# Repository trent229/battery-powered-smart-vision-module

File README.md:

# Battery-Powered Smart Vision Module

## Overview

The Battery-Powered Smart Vision Module is a compact embedded vision system built around the Seeed Studio XIAO ESP32S3 Sense. The project demonstrates battery-powered embedded design, Wi-Fi camera streaming, and low-power operation for robotics and remote monitoring applications.

This project serves as the foundation for the Sure Sight Security platform while demonstrating embedded systems engineering principles including power management, schematic design, firmware development, and hardware integration.

---

## Project Objectives

- Design a battery-powered embedded vision module.
- Stream live video over Wi-Fi.
- Operate from a rechargeable LiPo battery.
- Develop custom hardware for production.
- Demonstrate professional embedded engineering documentation.

---

## Course Outcomes

This project demonstrates:

- Embedded microcontroller selection
- Battery-powered embedded design
- Camera integration
- Vision sensing
- Schematic development
- PCB development
- Embedded firmware
- Professional engineering documentation

---

## Hardware

- Seeed Studio XIAO ESP32S3 Sense
- OV2640 Camera
- 3.7V LiPo Battery
- USB-C Charging
- Wi-Fi Connectivity

---

## Software

- Arduino IDE
- ESP32 Arduino Framework
- Git
- GitHub
- Visual Studio Code

---

## Repository Structure

```
docs/
firmware/
hardware/
media/
website/
```

---

## Current Status

🟢 Repository Created

🟢 Initial Folder Structure Complete

🟡 Hardware Design In Progress

⚪ PCB Design

⚪ Firmware Development

⚪ Testing

⚪ Final Documentation

---

## Future Improvements

- Battery Monitoring
- Motion Detection
- Custom PCB
- Improved Camera Module
- Power Optimization
- Weather Resistant Enclosure

---

## License

MIT License

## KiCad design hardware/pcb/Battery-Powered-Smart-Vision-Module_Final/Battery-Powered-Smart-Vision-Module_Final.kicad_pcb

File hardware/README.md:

# Battery-Powered Smart Vision Module

## Hardware

- XIAO ESP32S3 Sense
- LiPo Battery
- USB-C Charging

## Features

- Battery powered
- Wi-Fi camera
- Motion detection

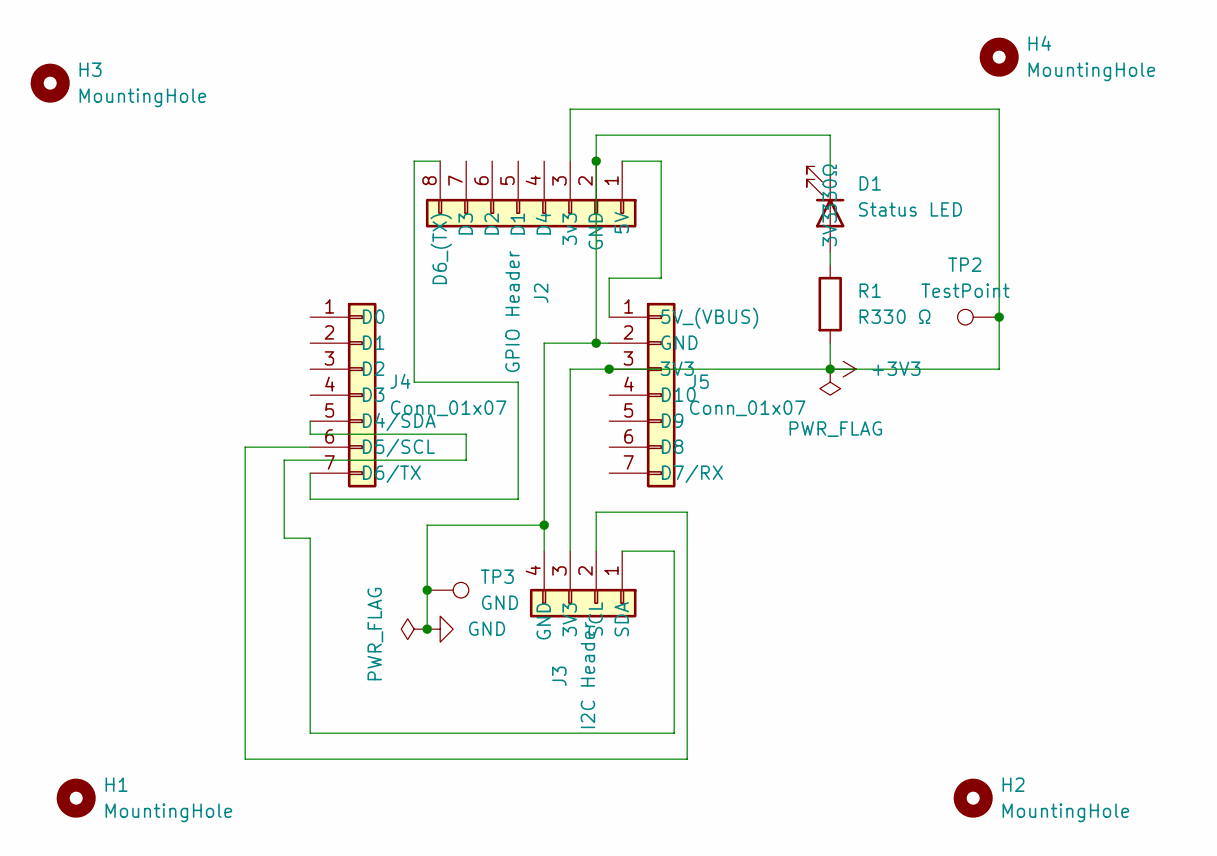
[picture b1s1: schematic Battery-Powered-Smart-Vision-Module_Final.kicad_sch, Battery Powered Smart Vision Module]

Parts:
D1: Status LED; LED_D5.0mm
H1, H2, H3, H4: MountingHole; MountingHole_3.2mm_M3
J2: GPIO Header; PinHeader_1x08_P2.54mm_Vertical
J3: I2C Header; PinHeader_1x04_P2.54mm_Vertical
J4, J5: Conn_01x07; PinHeader_1x07_P2.54mm_Vertical
R1: R330 Ω; R_Axial_DIN0207_L6.3mm_D2.5mm_P7.62mm_Horizontal
TP2: TestPoint; TestPoint_Loop_D3.80mm_Drill2.8mm
TP3: GND; TestPoint_Loop_D3.80mm_Drill2.8mm

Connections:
+3V3: J2.3 (3v3), J3.3 (3V3), J5.3 (3V3), R1.2, TP2.1 (1_1)
GND: D1.1 (3V3), J2.2 (GND), J3.4 (GND), J5.2 (GND), TP3.1 (1_1)
unnamed: D1.2 (330Ω), R1.1
unnamed: J2.1 (5V), J5.1 (5V_(VBUS))
unnamed: J2.8 (D6_(TX)), J4.7 (D6/TX)
unnamed: J3.2 (SCL), J4.6 (D5/SCL)
unnamed: J3.1 (SDA), J4.5 (D4/SDA)

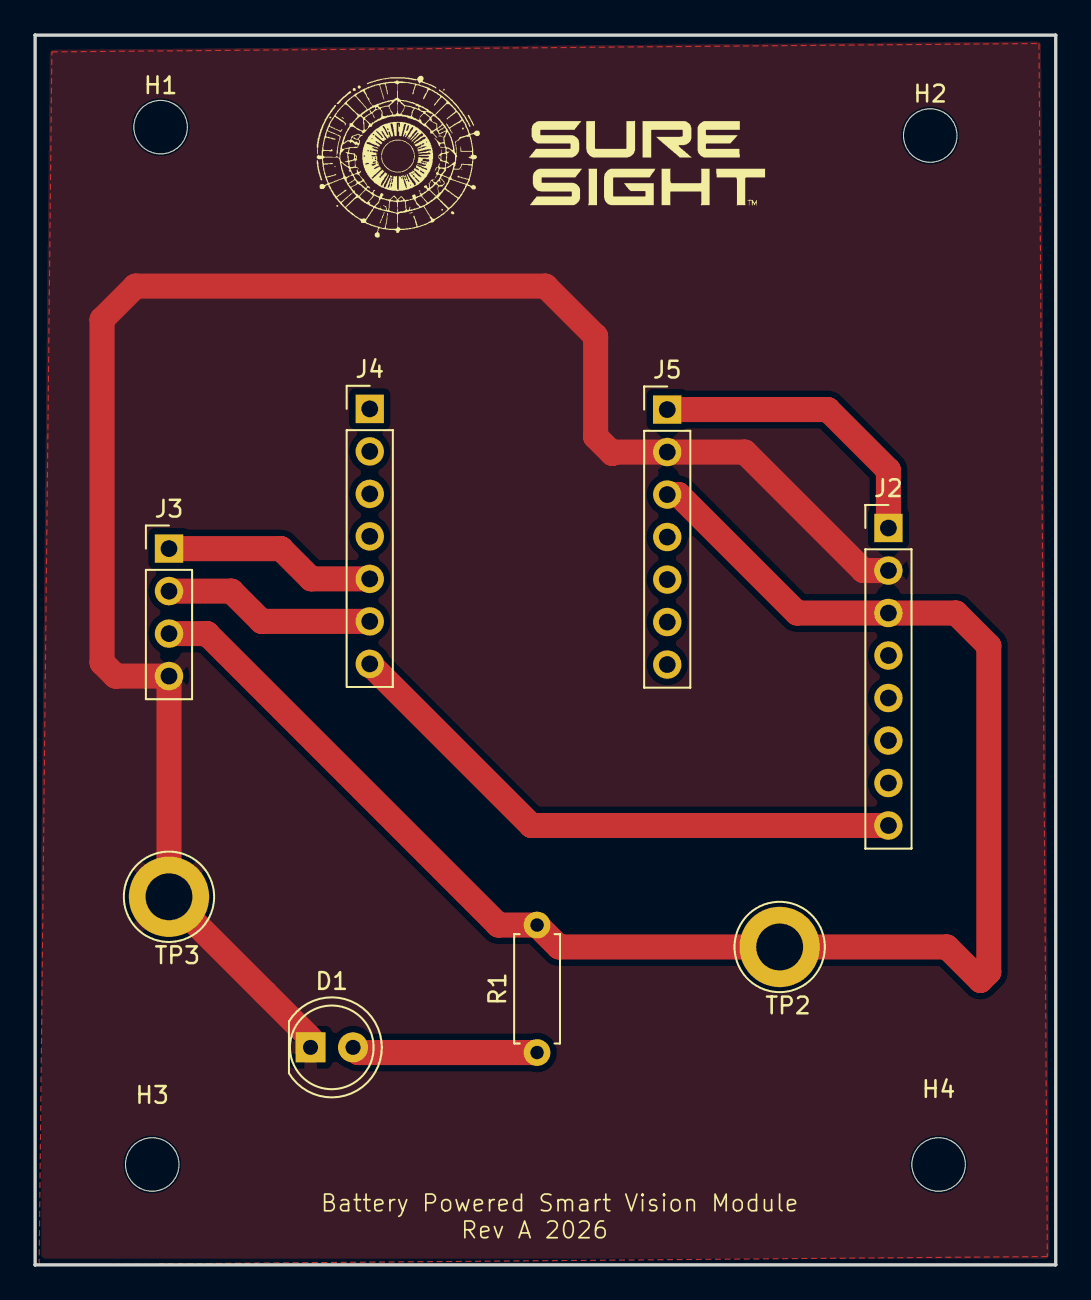
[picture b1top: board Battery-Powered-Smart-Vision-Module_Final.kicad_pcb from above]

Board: 2 copper layers, 61.0 x 73.5 mm, 12 parts (0 on the bottom side), 7 nets.

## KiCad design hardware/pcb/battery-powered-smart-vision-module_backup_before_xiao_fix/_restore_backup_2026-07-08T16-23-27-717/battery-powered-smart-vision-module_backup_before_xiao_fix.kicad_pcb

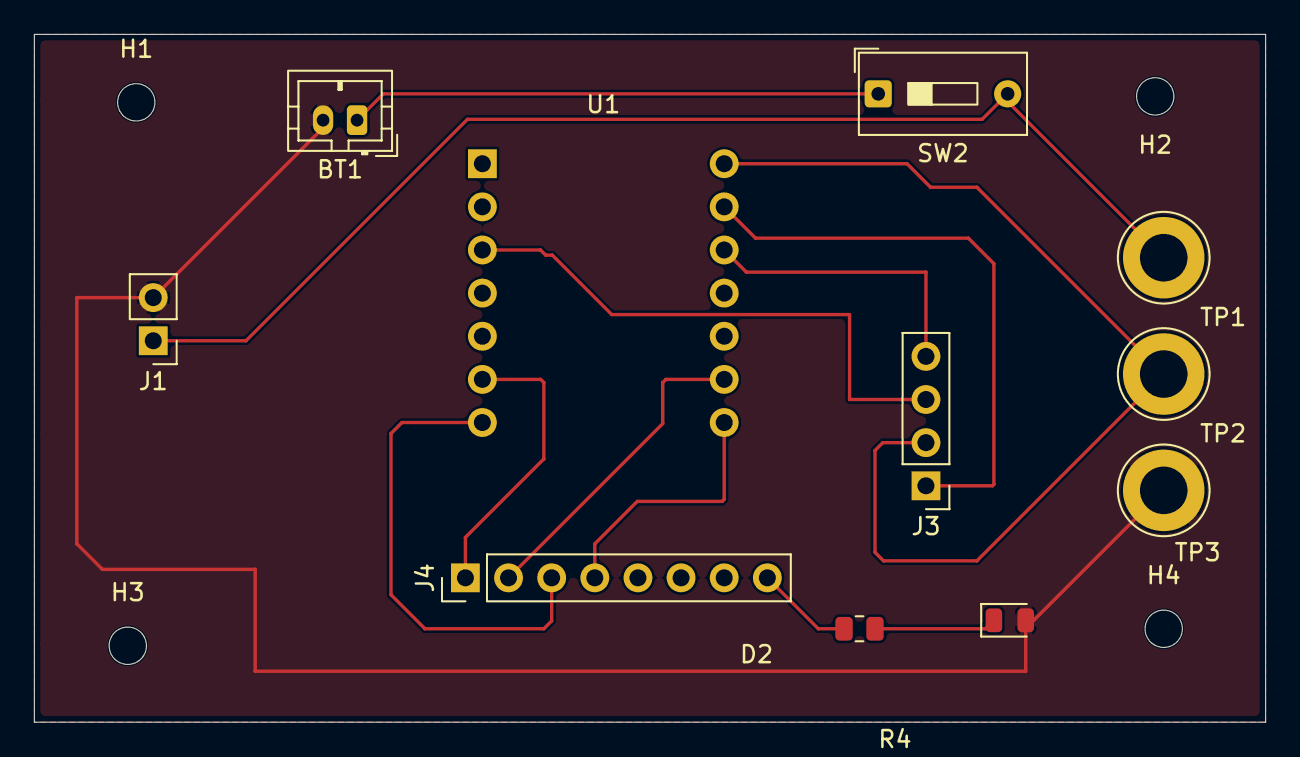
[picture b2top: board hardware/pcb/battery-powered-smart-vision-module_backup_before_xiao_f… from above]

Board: 2 copper layers, 72.5 x 40.5 mm, 15 parts (0 on the bottom side), 13 nets.

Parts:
BT1: LiPo Battery; JST_PH_B2B-PH-K_1x02_P2.00mm_Vertical
D2: LED; LED_0805_2012Metric
H1, H2, H3, H4: MountingHole; MountingHole_2.2mm_M2
J1: Conn_01x02; PinHeader_1x02_P2.54mm_Vertical
J3: I2C Header; PinHeader_1x04_P2.54mm_Vertical
J4: GPIO Header; PinHeader_1x08_P2.54mm_Vertical
R4: 330; R_0805_2012Metric
SW2: SW_SPST; SW_DIP_SPSTx01_Slide_9.78x4.72mm_W7.62mm_P2.54mm
TP1: BAT; TestPoint_Loop_D3.80mm_Drill2.8mm
TP2: 3V3; TestPoint_Loop_D3.80mm_Drill2.8mm
TP3: GND; TestPoint_Loop_D3.80mm_Drill2.8mm
U1: XIAO_ESP32S3_Sense_Socket_U1

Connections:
+3.3V: J3.2, TP2.1 (1_1), U1.2 (3V3)
GND: BT1.2, D2.2 (A), J1.2, TP3.1 (1_1)
unnamed: BT1.1, SW2.1 (A)
unnamed: D2.1 (K), R4.1
unnamed: J1.1, SW2.2 (B), TP1.1 (1_1)
unnamed: J3.1, U1.4 (GND)
unnamed: J3.3, U1.5 (SDA)
unnamed: J3.4, U1.6 (SCL)
unnamed: J4.1, U1.11 (TX)
unnamed: J4.2, U1.12 (RX)
unnamed: J4.3, U1.13 (GIPO)
unnamed: J4.4, U1.14 (GIPO_)
unnamed: J4.8, R4.2

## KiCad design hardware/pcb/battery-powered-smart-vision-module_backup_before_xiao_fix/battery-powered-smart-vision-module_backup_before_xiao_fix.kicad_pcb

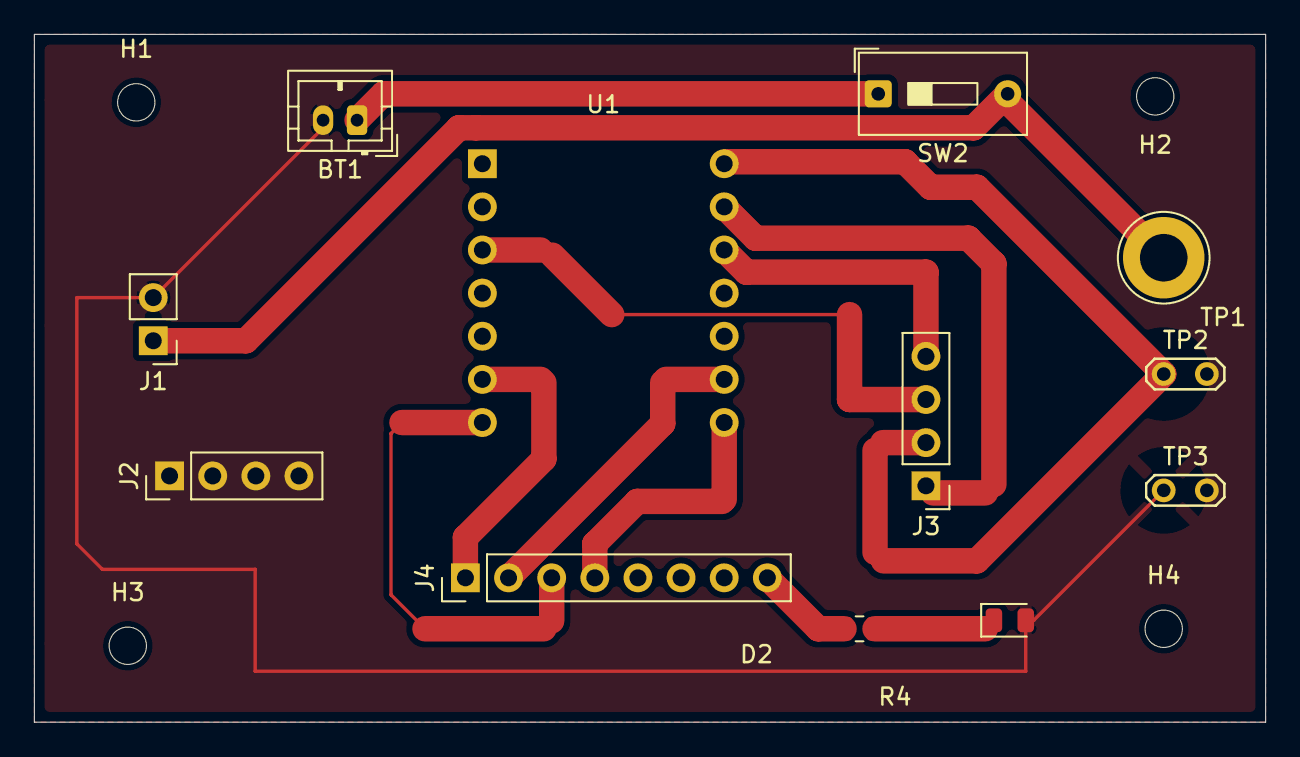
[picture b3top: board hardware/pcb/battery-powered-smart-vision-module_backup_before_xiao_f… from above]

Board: 2 copper layers, 72.5 x 40.5 mm, 16 parts (0 on the bottom side), 14 nets.

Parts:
BT1: LiPo Battery; JST_PH_B2B-PH-K_1x02_P2.00mm_Vertical
D2: LED; LED_0805_2012Metric
H1, H2, H3, H4: MountingHole; MountingHole_2.2mm_M2
J1: Conn_01x02; PinHeader_1x02_P2.54mm_Vertical
J2, J3: I2C Header; PinHeader_1x04_P2.54mm_Vertical
J4: GPIO Header; PinHeader_1x08_P2.54mm_Vertical
R4: 330; R_0805_2012Metric
SW2: SW_SPST; SW_DIP_SPSTx01_Slide_9.78x4.72mm_W7.62mm_P2.54mm
TP1: 3V3; TestPoint_Loop_D3.80mm_Drill2.8mm
TP2: 5V; TestPoint_2Pads_Pitch2.54mm_Drill0.8mm
TP3: GND; TestPoint_2Pads_Pitch2.54mm_Drill0.8mm
U1: XIAO_ESP32S3_Sense_Socket_U1

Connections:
+5V: J4.1 (5V), TP2.1 (1_1), U1.2 (5V)
GND: BT1.2, D2.2 (A), J1.2, J2.1, TP3.1 (1_1)
unnamed: BT1.1, SW2.1 (A)
unnamed: D2.1 (K), R4.2
unnamed: J1.1, SW2.2 (B)
unnamed: J2.2, J4.4 (D0), R4.1, TP1.1 (1_1), U1.8 (D10_(GPIO9))
unnamed: J2.3, U1.11 (D5_SCL_(GPIO6))
unnamed: J2.4, U1.9 (D4_SDA_(GPIO5))
unnamed: J4.3 (3V3), U1.6 (3V3)
unnamed: J4.5 (D1), U1.10 (D9_(GPIO8))
unnamed: J4.6 (D2), U1.12 (D8_(GPIO7))
unnamed: J4.7 (D3), U1.14 (D7_RX_(GPIO44))
unnamed: J4.8 (D6_(TX)), U1.13 (D6_TX_(GPIO43))
unnamed: J4.2 (GND), U1.4 (GND)
